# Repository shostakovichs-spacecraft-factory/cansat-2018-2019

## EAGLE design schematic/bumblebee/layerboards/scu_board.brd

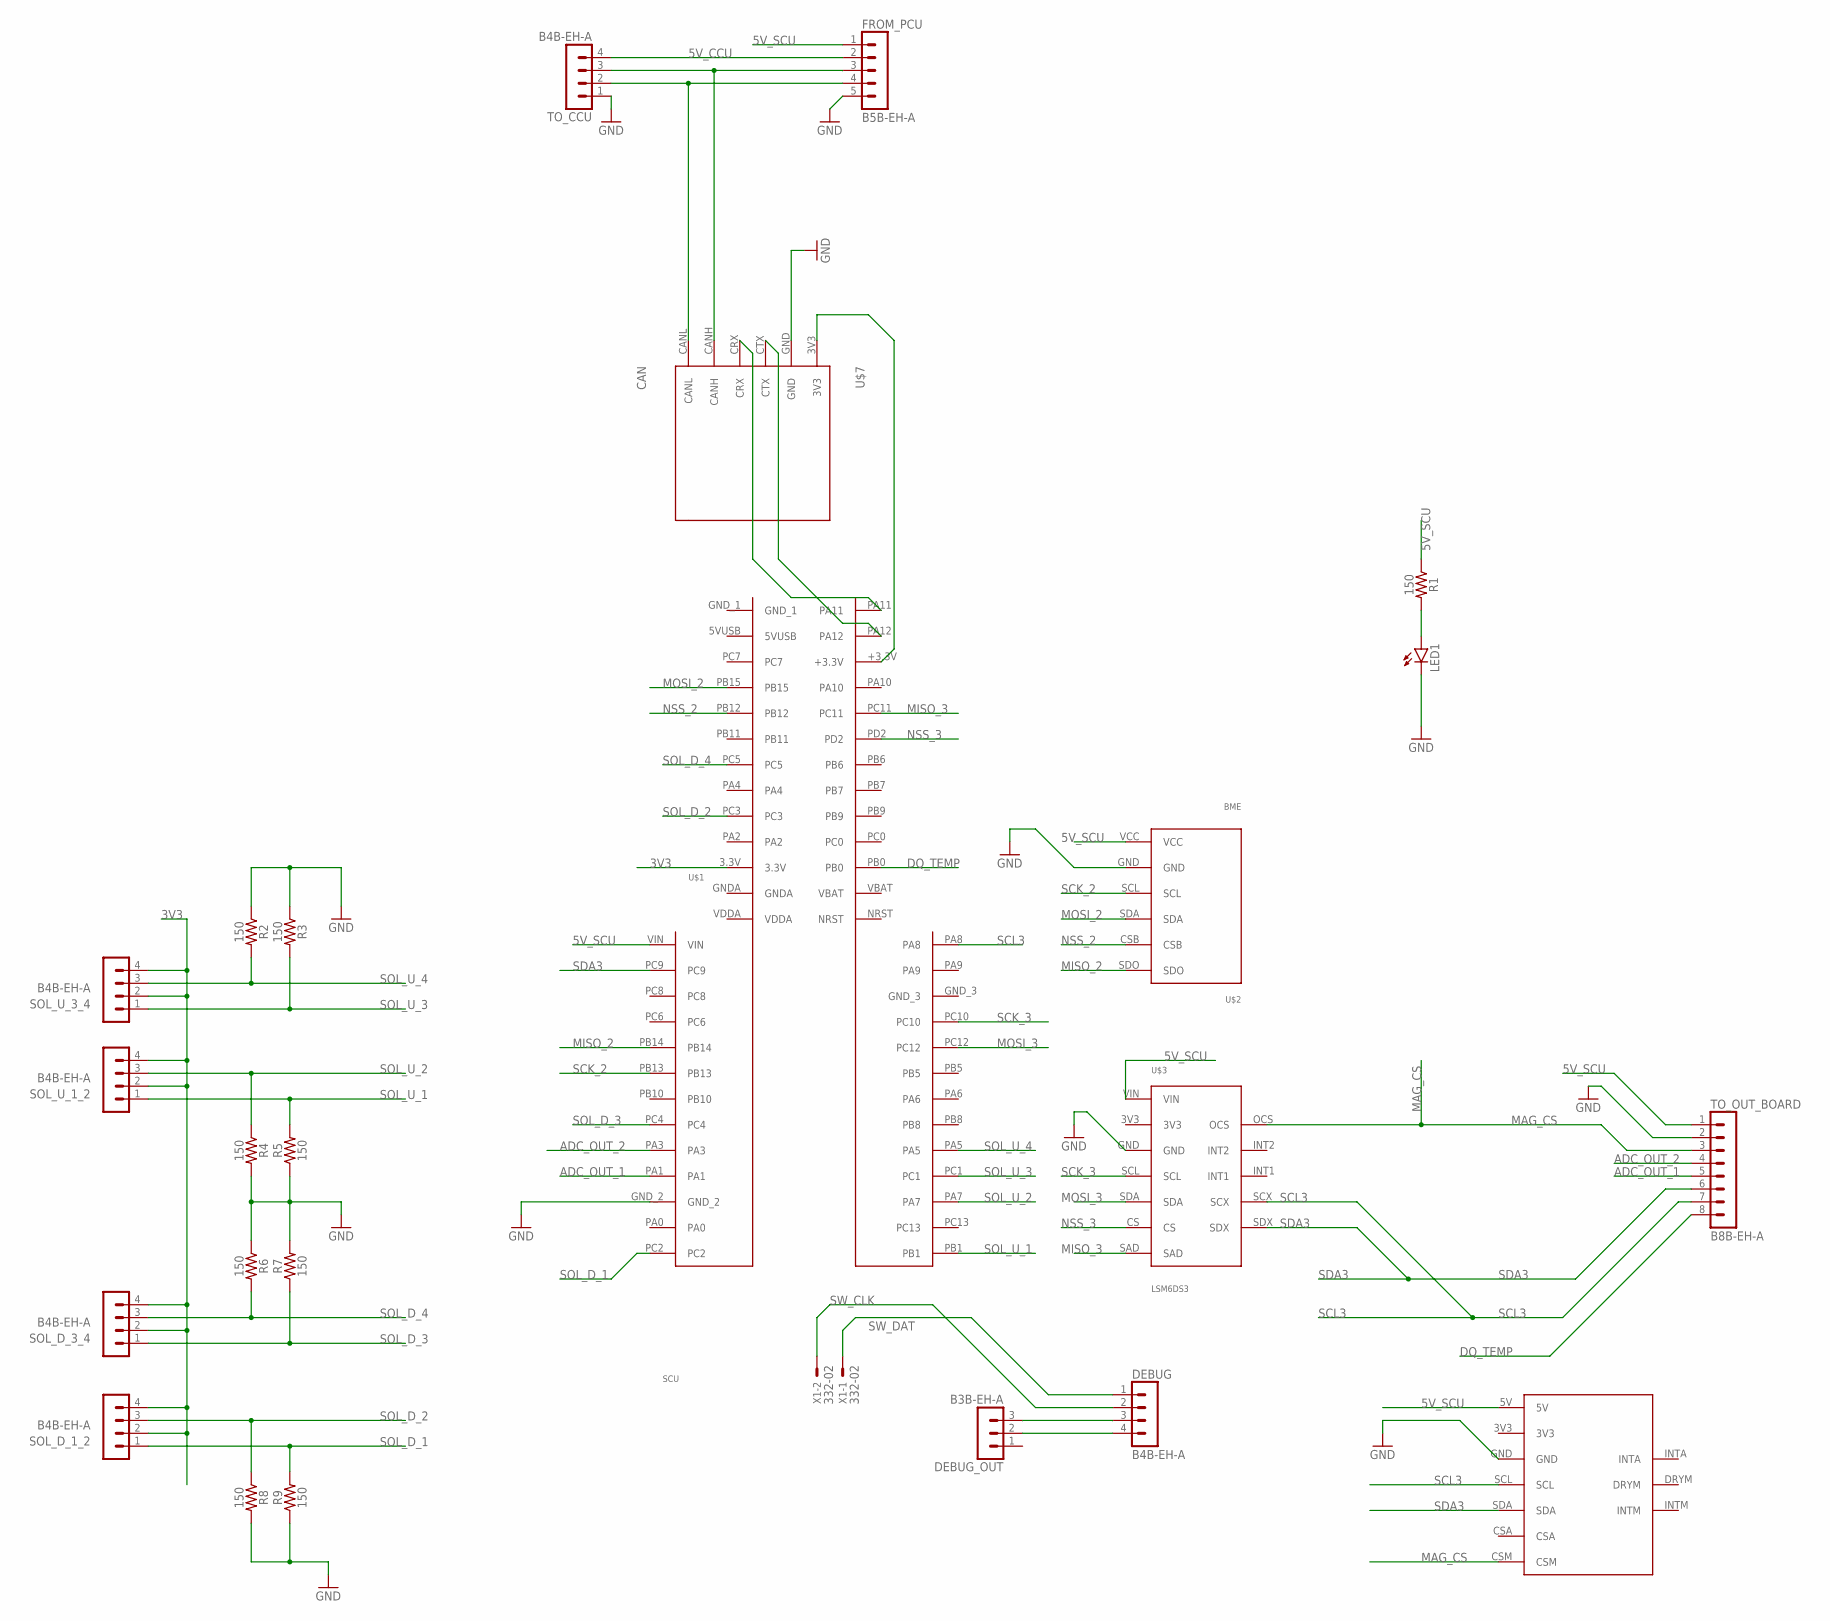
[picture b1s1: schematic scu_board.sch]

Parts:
DEBUG: B4B-EH-A
DEBUG_OUT: B3B-EH-A
FROM_PCU: B5B-EH-A
LED1: LED5MM
R1, R2, R3, R4, R5, R6, R7, R8, R9: 150; AXIAL-0.3
SOL_D_1_2, SOL_D_3_4: B4B-EH-A
SOL_U_1_2, SOL_U_3_4: B4B-EH-A
TO_CCU: B4B-EH-A
TO_OUT_BOARD: B8B-EH-A
U$1: SCU
U$2: BME
U$3: LSM6DS3
U$4: LSM303C
U$7: CAN
X1: 332-02

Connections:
3V3: SOL_D_1_2.2, SOL_D_1_2.4, SOL_D_3_4.2, SOL_D_3_4.4, SOL_U_1_2.2, SOL_U_1_2.4, SOL_U_3_4.2, SOL_U_3_4.4, U$1.3.3V
5V_CCU: FROM_PCU.2, TO_CCU.4
5V_SCU: FROM_PCU.1, R1.P$1 (1), TO_OUT_BOARD.1, U$1.VIN, U$2.VCC, U$3.VIN, U$4.5V
ADC_OUT_1: TO_OUT_BOARD.5, U$1.PA1
ADC_OUT_2: TO_OUT_BOARD.4, U$1.PA3
DQ_TEMP: TO_OUT_BOARD.8, U$1.PB0
GND: FROM_PCU.5, LED1.K (C), R2.P$1 (1), R3.P$1 (1), R4.P$2 (2), R5.P$1 (1), R6.P$1 (1), R7.P$2 (2), R8.P$2 (2), R9.P$1 (1), TO_CCU.1, TO_OUT_BOARD.2, U$1.GND_2, U$2.GND, U$3.GND, U$4.GND, U$7.GND
MAG_CS: TO_OUT_BOARD.3, U$3.OCS, U$4.CSM
MISO_2: U$1.PB14, U$2.SDO
MISO_3: U$1.PC11, U$3.SAD
MOSI_2: U$1.PB15, U$2.SDA
MOSI_3: U$1.PC12, U$3.SDA
unnamed: U$1.PA11, U$7.CRX
unnamed: U$1.PA12, U$7.CTX
unnamed: U$1.+3.3V, U$7.3V3
unnamed: LED1.A, R1.P$2 (2)
unnamed: FROM_PCU.3, TO_CCU.3, U$7.CANH
unnamed: FROM_PCU.4, TO_CCU.2, U$7.CANL
unnamed: DEBUG.3, DEBUG_OUT.3
unnamed: DEBUG.4, DEBUG_OUT.2
NSS_2: U$1.PB12, U$2.CSB
NSS_3: U$1.PD2, U$3.CS
SCK_2: U$1.PB13, U$2.SCL
SCK_3: U$1.PC10, U$3.SCL
SCL3: TO_OUT_BOARD.7, U$1.PA8, U$3.SCX, U$4.SCL
SDA3: TO_OUT_BOARD.6, U$1.PC9, U$3.SDX, U$4.SDA
SOL_D_1: R9.P$2 (2), SOL_D_1_2.1, U$1.PC2
SOL_D_2: R8.P$1 (1), SOL_D_1_2.3, U$1.PC3
SOL_D_3: R7.P$1 (1), SOL_D_3_4.1, U$1.PC4
SOL_D_4: R6.P$2 (2), SOL_D_3_4.3, U$1.PC5
SOL_U_1: R5.P$2 (2), SOL_U_1_2.1, U$1.PB1
SOL_U_2: R4.P$1 (1), SOL_U_1_2.3, U$1.PA7
SOL_U_3: R3.P$2 (2), SOL_U_3_4.1, U$1.PC1
SOL_U_4: R2.P$2 (2), SOL_U_3_4.3, U$1.PA5
SW_CLK: DEBUG.2, X1.2
SW_DAT: DEBUG.1, X1.1

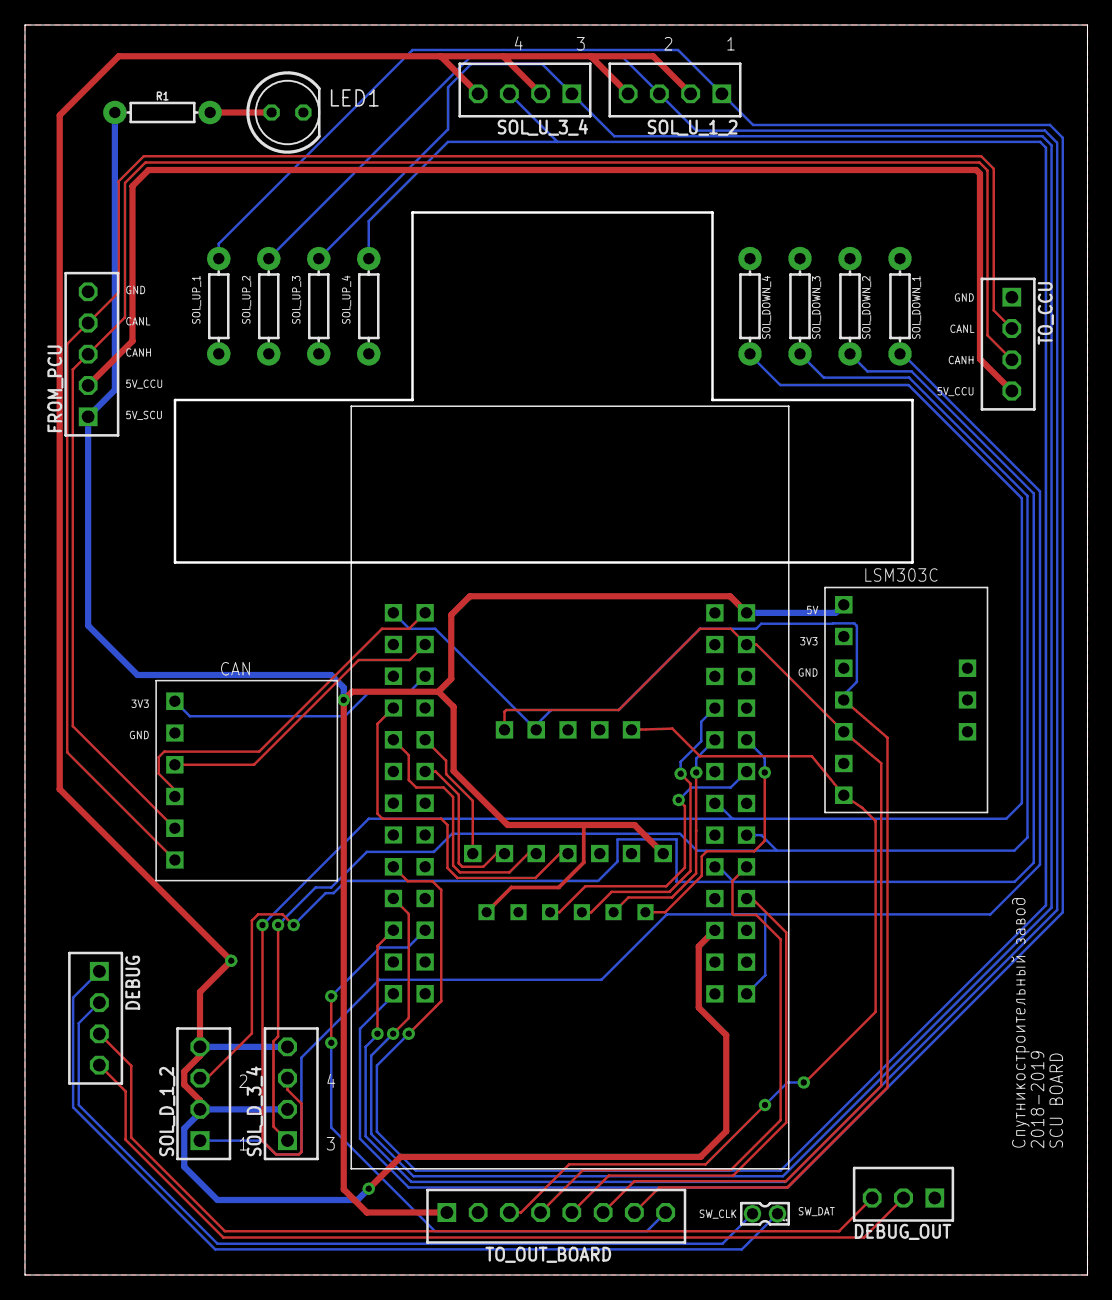
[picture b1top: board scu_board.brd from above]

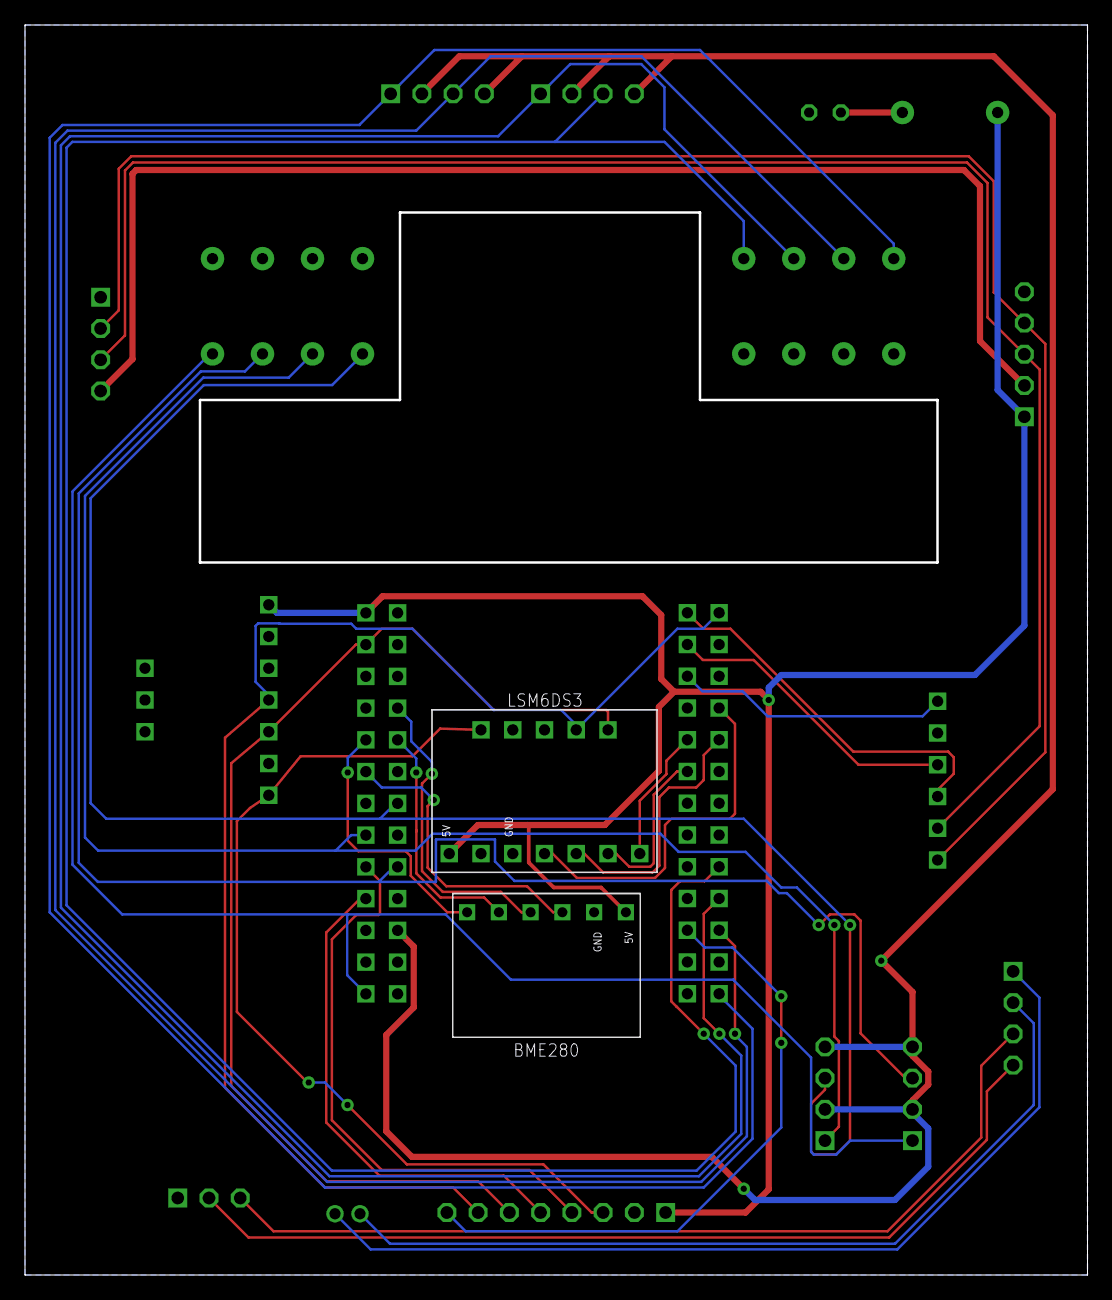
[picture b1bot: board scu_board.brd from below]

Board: 2 copper layers, 85.0 x 100.0 mm, 25 parts (2 on the bottom side), 36 nets.

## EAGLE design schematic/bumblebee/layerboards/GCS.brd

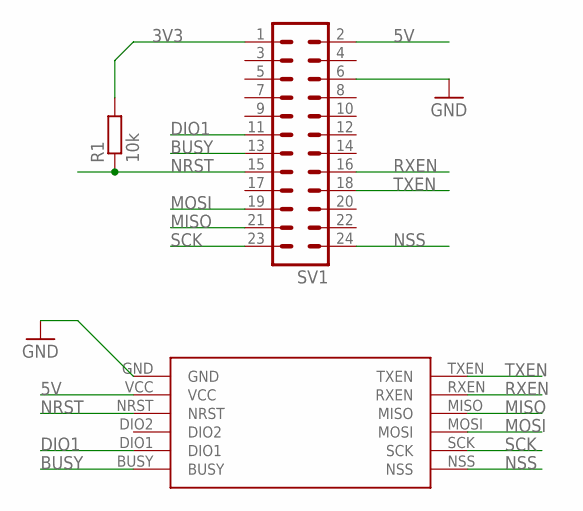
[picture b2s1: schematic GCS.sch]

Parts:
R1: 10k; 0207/10
SV1: MA12-2
U$1: E22_PLATE

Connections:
3V3: R1.2, SV1.1
5V: SV1.2, U$1.VCC
BUSY: SV1.13, U$1.BUSY
DIO1: SV1.11, U$1.DIO1
GND: SV1.6, U$1.GND
MISO: SV1.21, U$1.MISO
MOSI: SV1.19, U$1.MOSI
NRST: R1.1, SV1.15, U$1.NRST
NSS: SV1.24, U$1.NSS
RXEN: SV1.16, U$1.RXEN
SCK: SV1.23, U$1.SCK
TXEN: SV1.18, U$1.TXEN

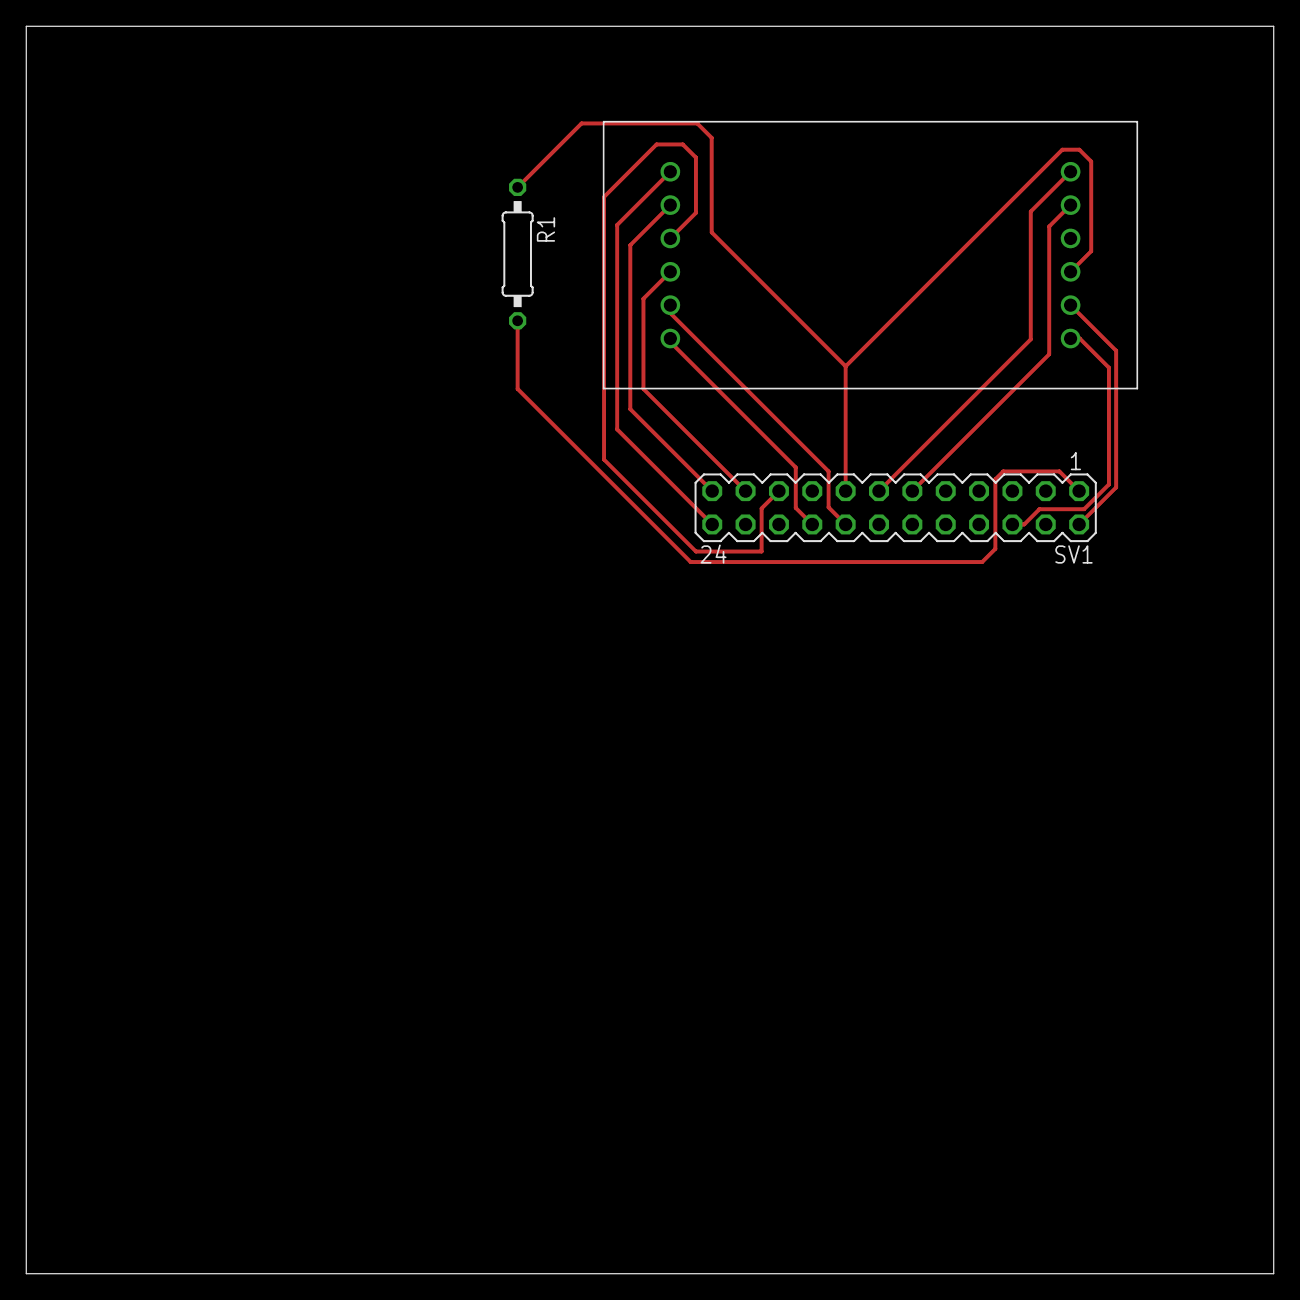
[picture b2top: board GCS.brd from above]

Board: 2 copper layers, 95.0 x 95.0 mm, 3 parts (0 on the bottom side), 12 nets.

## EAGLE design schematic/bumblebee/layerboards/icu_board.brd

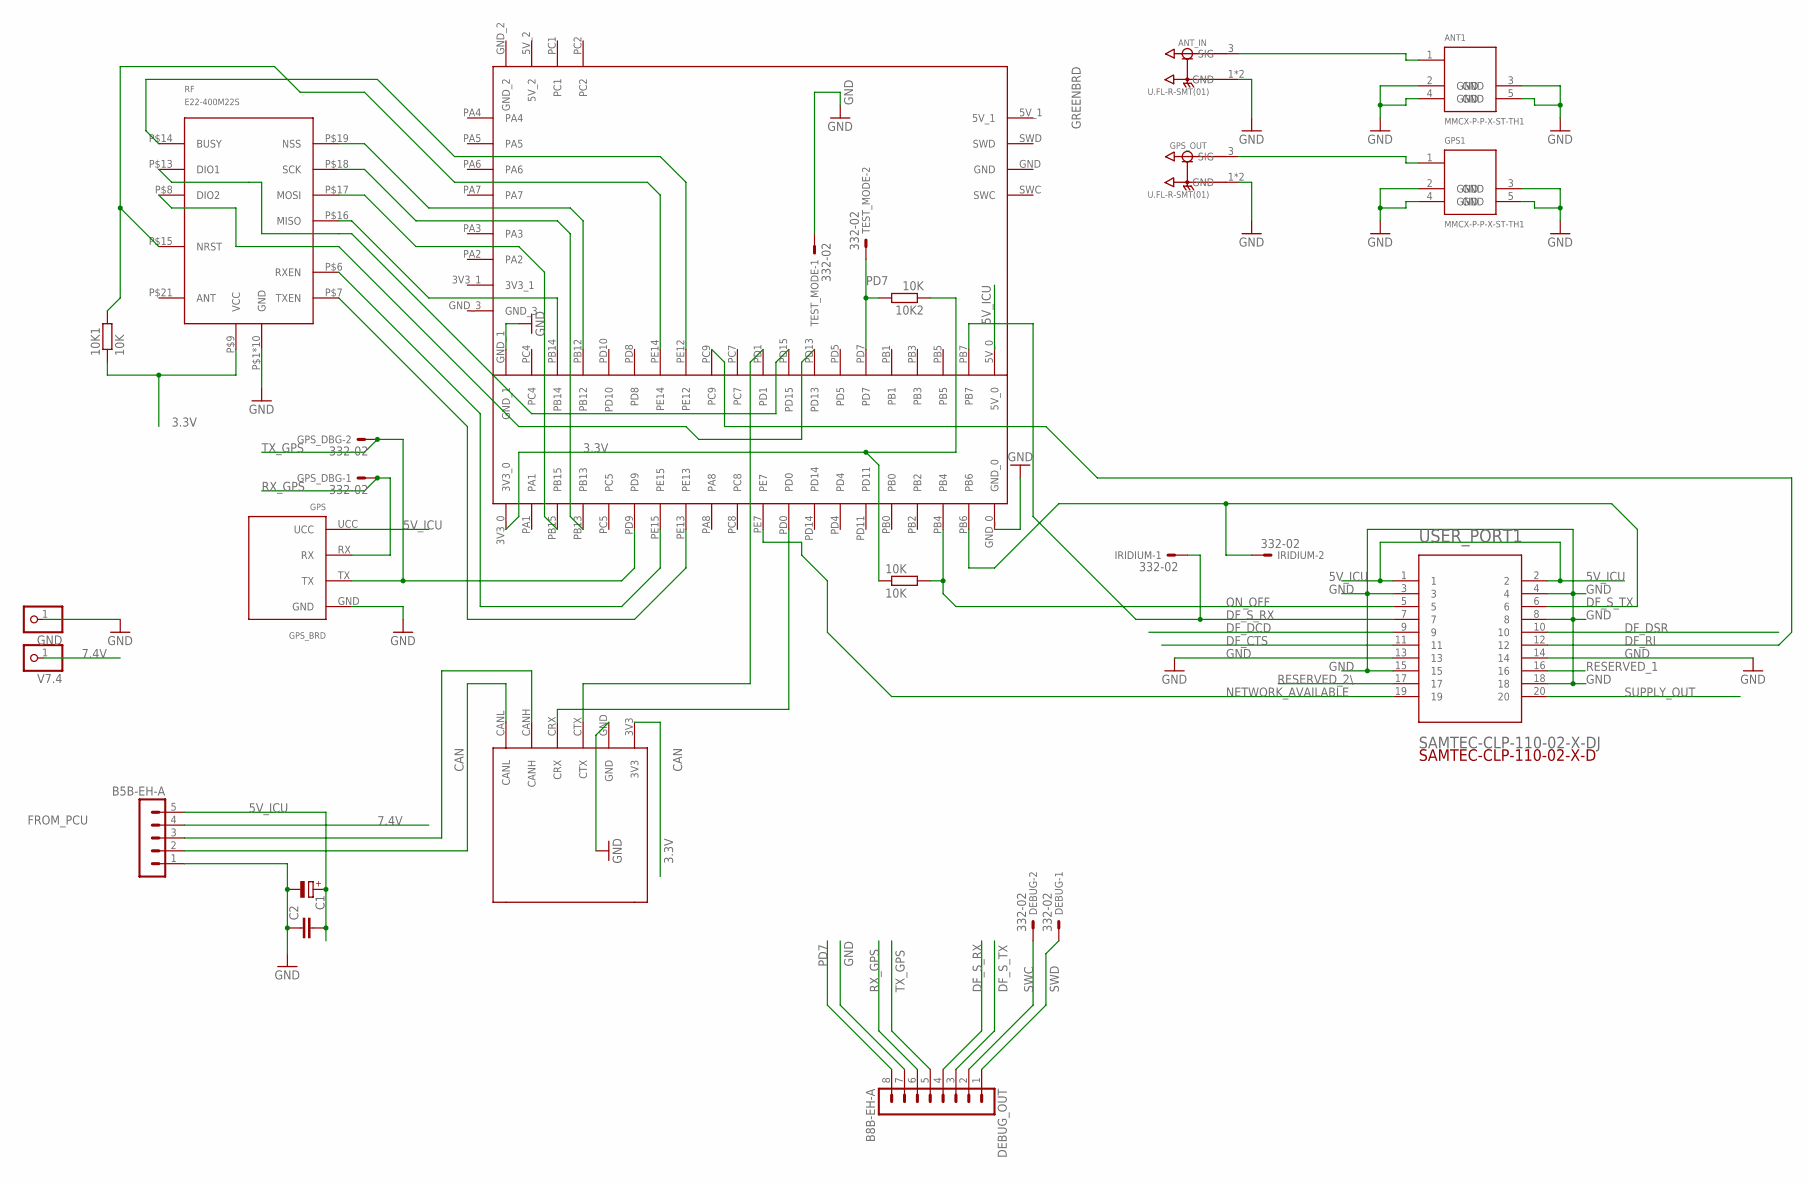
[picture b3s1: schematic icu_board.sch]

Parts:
10K, 10K1, 10K2: 10K; 0204/7
ANT1: MMCX-P-P-X-ST-TH1
ANT_IN: U.FL-R-SMT(01); HRS_U.FL-R-SMT(01)
C1: CPOL-EUE3.5-8; E3,5-8
C2: C2.5/2; C2.5-2
CAN: CAN
DEBUG: 332-02
DEBUG_OUT: B8B-EH-A
FROM_PCU: B5B-EH-A
GND: PINHD-1X1; 1X01
GPS1: MMCX-P-P-X-ST-TH1
GPS_BRD: GPS
GPS_DBG: 332-02
GPS_OUT: U.FL-R-SMT(01); HRS_U.FL-R-SMT(01)
GREENBRD: ICU
IRIDIUM: 332-02
RF: E22-400M22S
TEST_MODE: 332-02
USER_PORT1: SAMTEC-CLP-110-02-X-DJ; SAMTEC-CLP-110-02-X-D
V7.4: PINHD-1X1; 1X01

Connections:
3.3V: 10K.1, 10K1.1, 10K2.1, CAN.3V3, GREENBRD.3V3_0, RF.P$9 (VCC)
5V_ICU: C1.+, C2.2, FROM_PCU.5, GPS_BRD.UCC, GREENBRD.5V_0, USER_PORT1.1, USER_PORT1.2
7.4V: FROM_PCU.4, V7.4.1
DF_CTS: USER_PORT1.11
DF_DCD: USER_PORT1.9
DF_DSR: USER_PORT1.10
DF_RI: GREENBRD.PC9, USER_PORT1.12
DF_S_RX: DEBUG_OUT.4, GREENBRD.PB7, IRIDIUM.1, USER_PORT1.7
DF_S_TX: DEBUG_OUT.3, GREENBRD.PB6, IRIDIUM.2, USER_PORT1.6
GND: ANT1.2 (GND), ANT1.3 (GND), ANT1.4 (GND), ANT1.5 (GND), ANT_IN.1 (GND), ANT_IN.2 (GND), C1.-, C2.1, CAN.GND, DEBUG_OUT.7, FROM_PCU.1, GND.1, GPS1.2 (GND), GPS1.3 (GND), GPS1.4 (GND), GPS1.5 (GND), GPS_BRD.GND, GPS_OUT.1 (GND), GPS_OUT.2 (GND), GREENBRD.GND_0, GREENBRD.GND_1, RF.P$1 (GND), RF.P$2 (GND), RF.P$3 (GND), RF.P$4 (GND), RF.P$5 (GND), RF.P$10 (GND), RF.P$11 (GND), RF.P$12 (GND), RF.P$20 (GND), RF.P$22 (GND), TEST_MODE.1, USER_PORT1.3, USER_PORT1.4, USER_PORT1.8, USER_PORT1.13, USER_PORT1.14, USER_PORT1.15, USER_PORT1.18
unnamed: CAN.CANH, FROM_PCU.3
unnamed: GREENBRD.PB12, RF.P$19 (NSS)
unnamed: CAN.CANL, FROM_PCU.2
unnamed: ANT1.1, ANT_IN.3 (SIG)
unnamed: GPS1.1, GPS_OUT.3 (SIG)
unnamed: GREENBRD.PE15, RF.P$6 (RXEN)
unnamed: GREENBRD.PB13, RF.P$18 (SCK)
unnamed: CAN.CRX, GREENBRD.PD0
unnamed: CAN.CTX, GREENBRD.PD1
unnamed: GREENBRD.PD15, RF.P$13 (DIO1)
unnamed: GREENBRD.PD13, RF.P$8 (DIO2)
unnamed: GREENBRD.PB15, RF.P$17 (MOSI)
unnamed: GREENBRD.PB14, RF.P$16 (MISO)
unnamed: GREENBRD.PE12, RF.P$14 (BUSY)
unnamed: 10K1.2, GREENBRD.PE14, RF.P$15 (NRST)
unnamed: GREENBRD.PE13, RF.P$7 (TXEN)
NETWORK_AVAILABLE: GREENBRD.PE7, USER_PORT1.19
ON_OFF: 10K.2, GREENBRD.PB4, USER_PORT1.5
PD7: 10K2.2, DEBUG_OUT.8, GREENBRD.PD7, TEST_MODE.2
RESERVED_1: USER_PORT1.16
RESERVED_2\: USER_PORT1.17
RX_GPS: DEBUG_OUT.6, GPS_BRD.RX, GPS_DBG.1
SUPPLY_OUT: USER_PORT1.20
SWC: DEBUG.2, DEBUG_OUT.2
SWD: DEBUG.1, DEBUG_OUT.1
TX_GPS: DEBUG_OUT.5, GPS_BRD.TX, GPS_DBG.2, GREENBRD.PD9

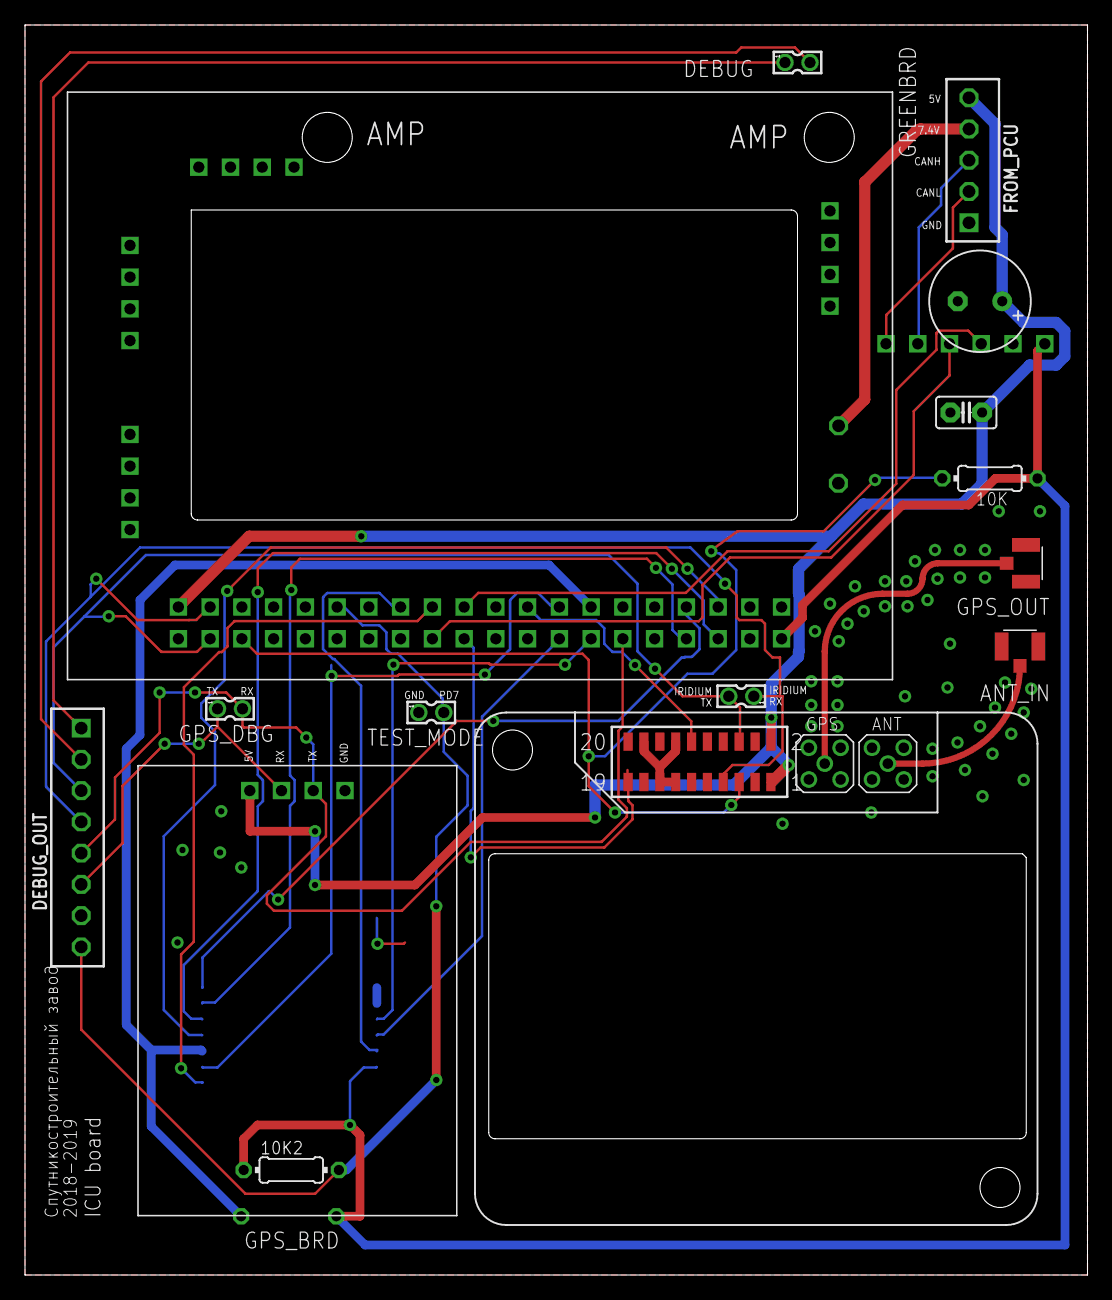
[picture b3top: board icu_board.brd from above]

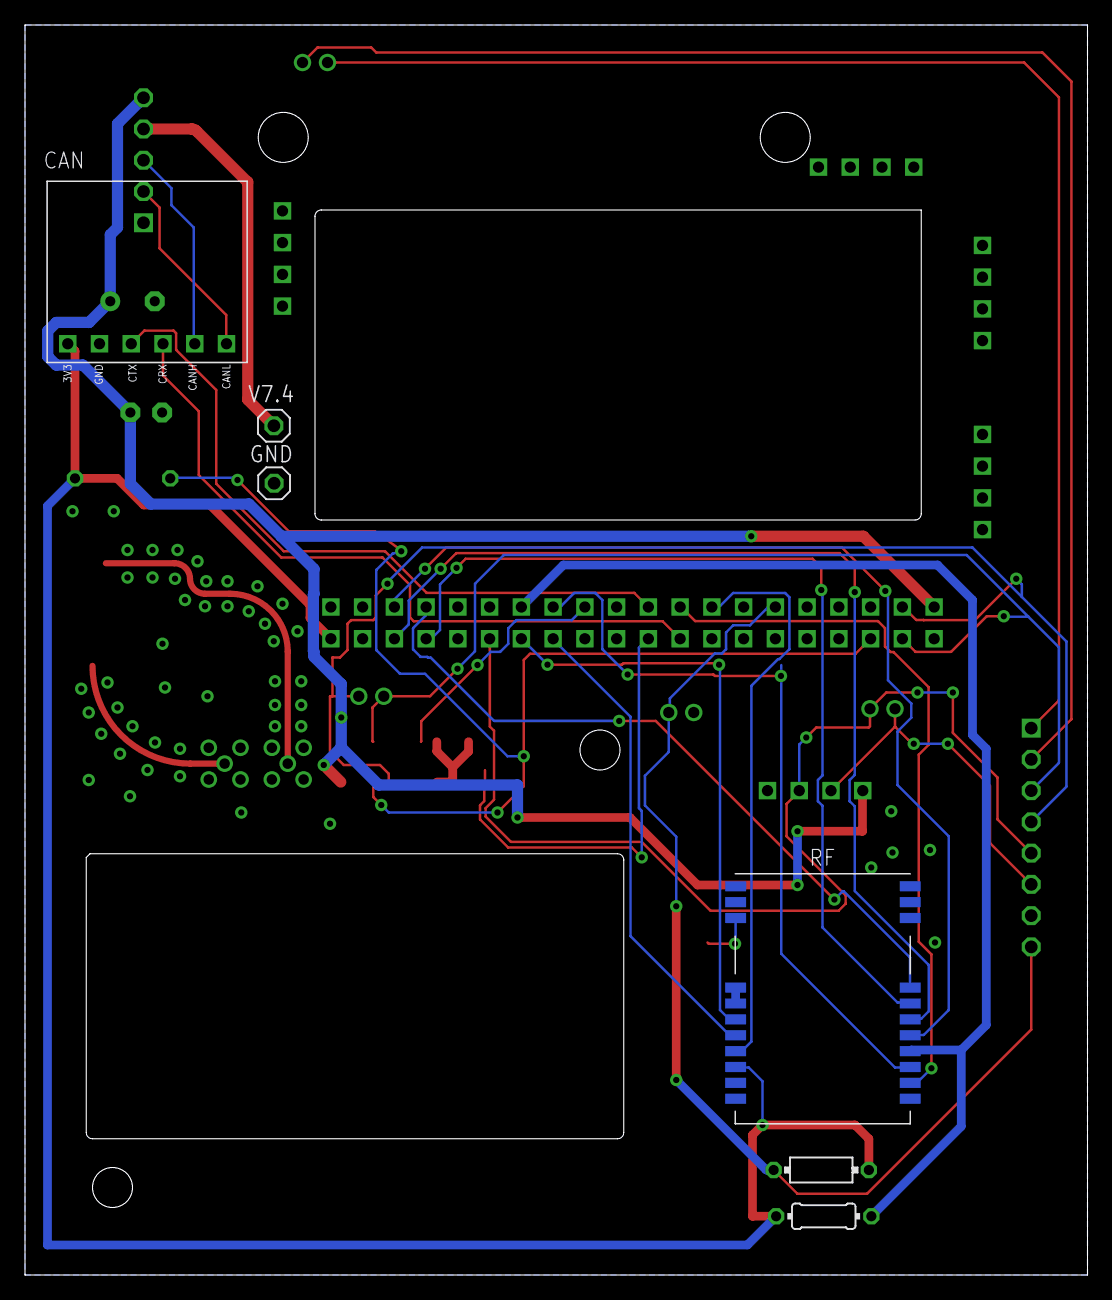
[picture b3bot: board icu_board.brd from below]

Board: 2 copper layers, 85.0 x 100.0 mm, 22 parts (5 on the bottom side), 30 nets.

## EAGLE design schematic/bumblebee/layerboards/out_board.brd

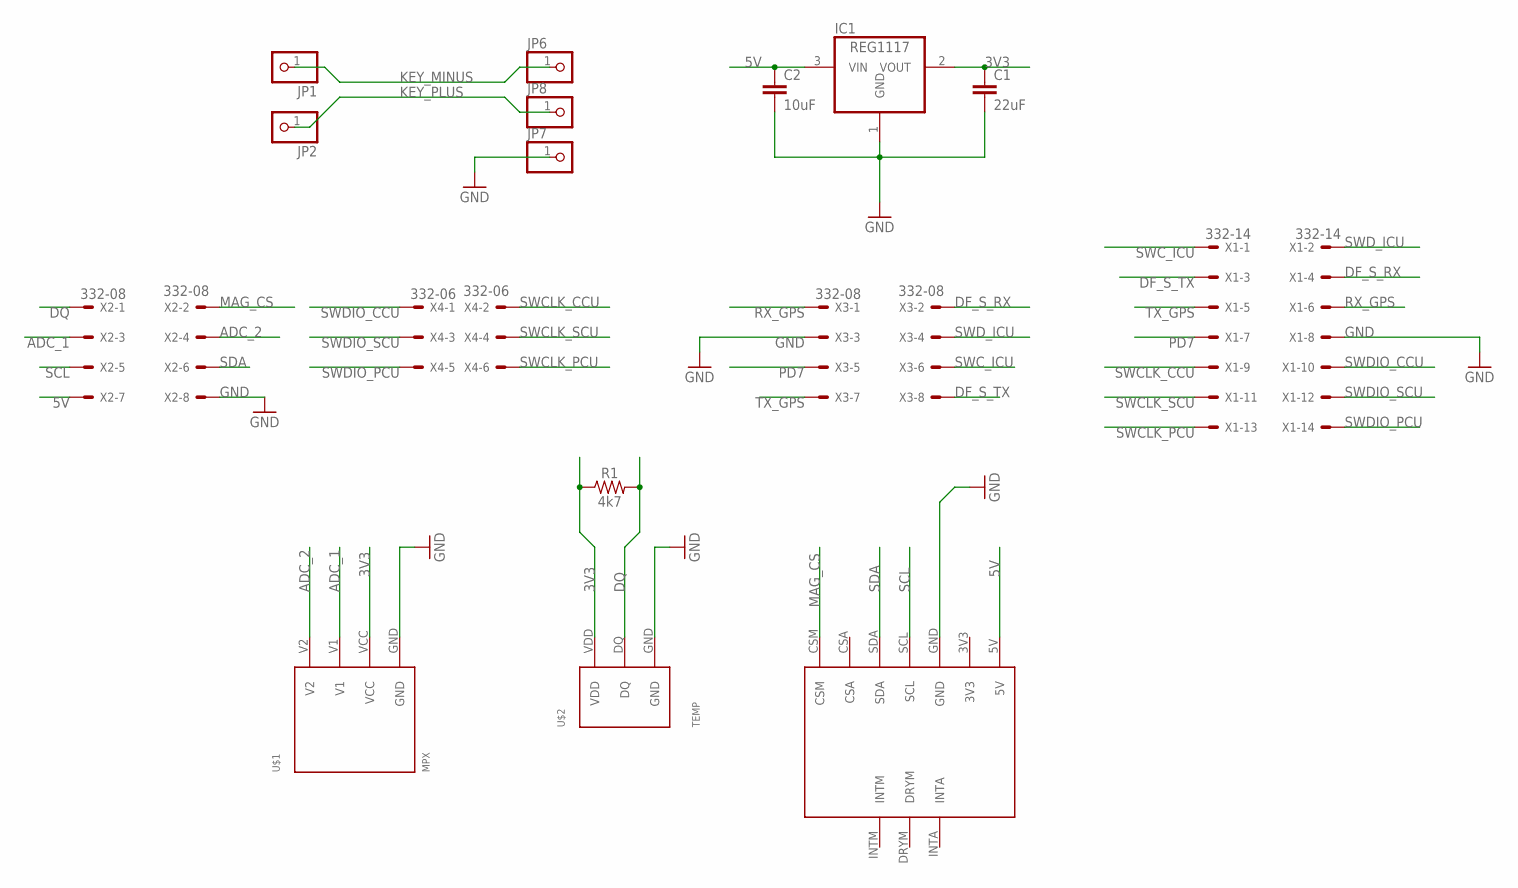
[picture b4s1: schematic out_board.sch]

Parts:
C1: 22uF; 0805
C2: 10uF; 0805
IC1: REG1117; SOT223
JP1, JP2, JP6, JP7, JP8: PINHD-1X1; 1X01
R1: 4k7; AXIAL-0.3
U$1: MPX
U$2: TEMP
U$3: LSM303C
X1: 332-14
X2, X3: 332-08
X4: 332-06

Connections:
3V3: C1.1, IC1.2 (VOUT), R1.P$1 (1), U$1.VCC, U$2.VDD
5V: C2.1, IC1.3 (VIN), U$3.5V, X2.7
ADC_1: U$1.V1, X2.3
ADC_2: U$1.V2, X2.4
DF_S_RX: X1.4, X3.2
DF_S_TX: X1.3, X3.8
DQ: R1.P$2 (2), U$2.DQ, X2.1
GND: C1.2, C2.2, IC1.1 (GND), JP7.1, U$1.GND, U$2.GND, U$3.GND, X1.8, X2.8, X3.3
KEY_MINUS: JP1.1, JP6.1
KEY_PLUS: JP2.1, JP8.1
MAG_CS: U$3.CSM, X2.2
PD7: X1.7, X3.5
RX_GPS: X1.6, X3.1
SCL: U$3.SCL, X2.5
SDA: U$3.SDA, X2.6
SWCLK_CCU: X1.9, X4.2
SWCLK_PCU: X1.13, X4.6
SWCLK_SCU: X1.11, X4.4
SWC_ICU: X1.1, X3.6
SWDIO_CCU: X1.10, X4.1
SWDIO_PCU: X1.14, X4.5
SWDIO_SCU: X1.12, X4.3
SWD_ICU: X1.2, X3.4
TX_GPS: X1.5, X3.7

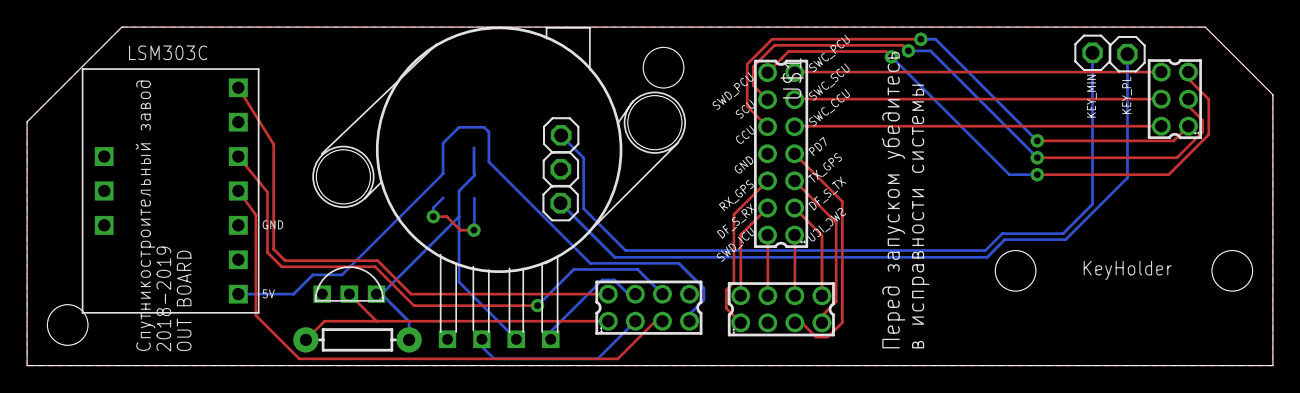
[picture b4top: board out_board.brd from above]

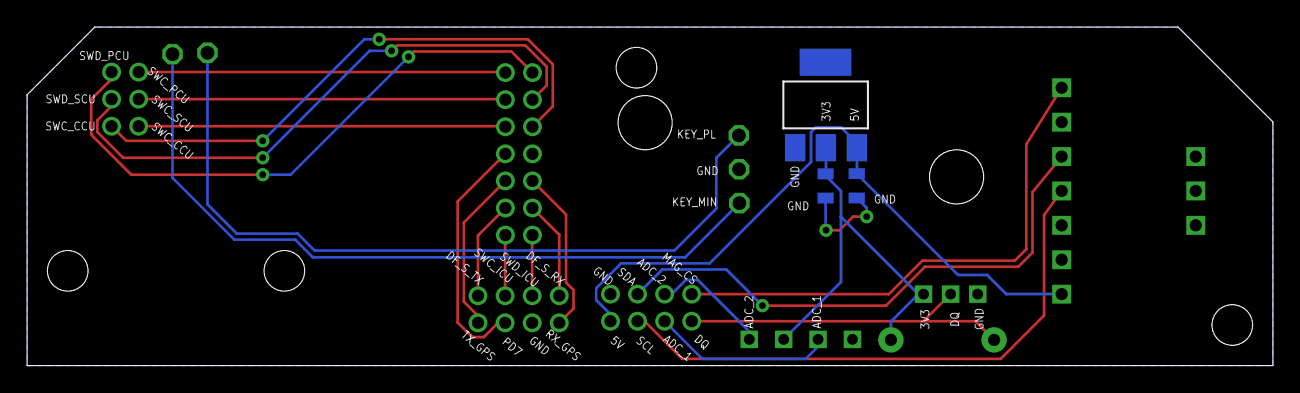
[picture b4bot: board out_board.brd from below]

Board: 2 copper layers, 92.0 x 25.0 mm, 16 parts (3 on the bottom side), 24 nets.

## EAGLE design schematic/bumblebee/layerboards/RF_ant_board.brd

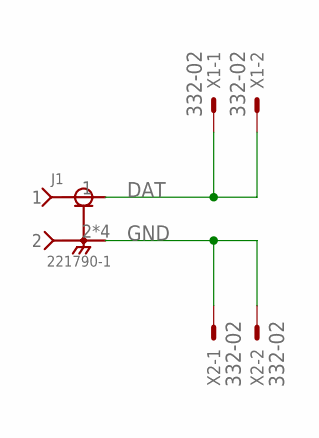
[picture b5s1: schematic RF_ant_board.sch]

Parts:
J1: 221790-1; TE_221790-1
X1, X2: 332-02

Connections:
DAT: J1.1, X1.1, X1.2
GND: J1.2, J1.3 (2), J1.4 (2), J1.5 (2), X2.1, X2.2

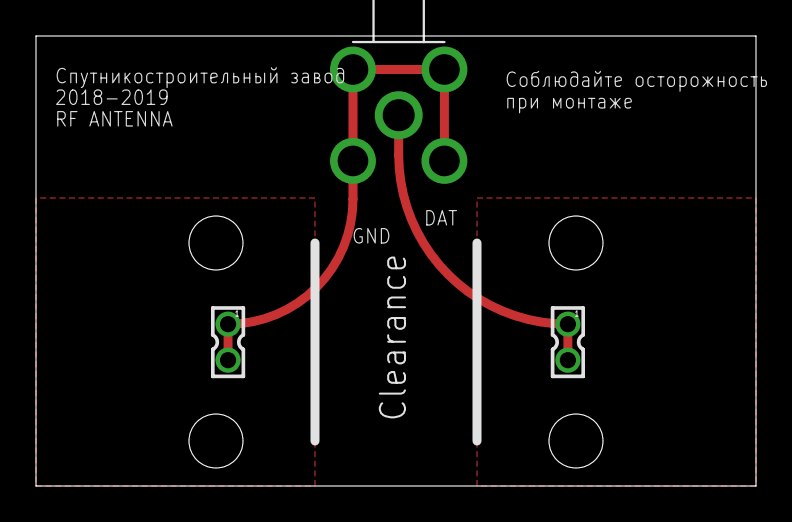
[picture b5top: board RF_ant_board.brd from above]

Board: 2 copper layers, 40.0 x 25.0 mm, 3 parts (0 on the bottom side), 2 nets.

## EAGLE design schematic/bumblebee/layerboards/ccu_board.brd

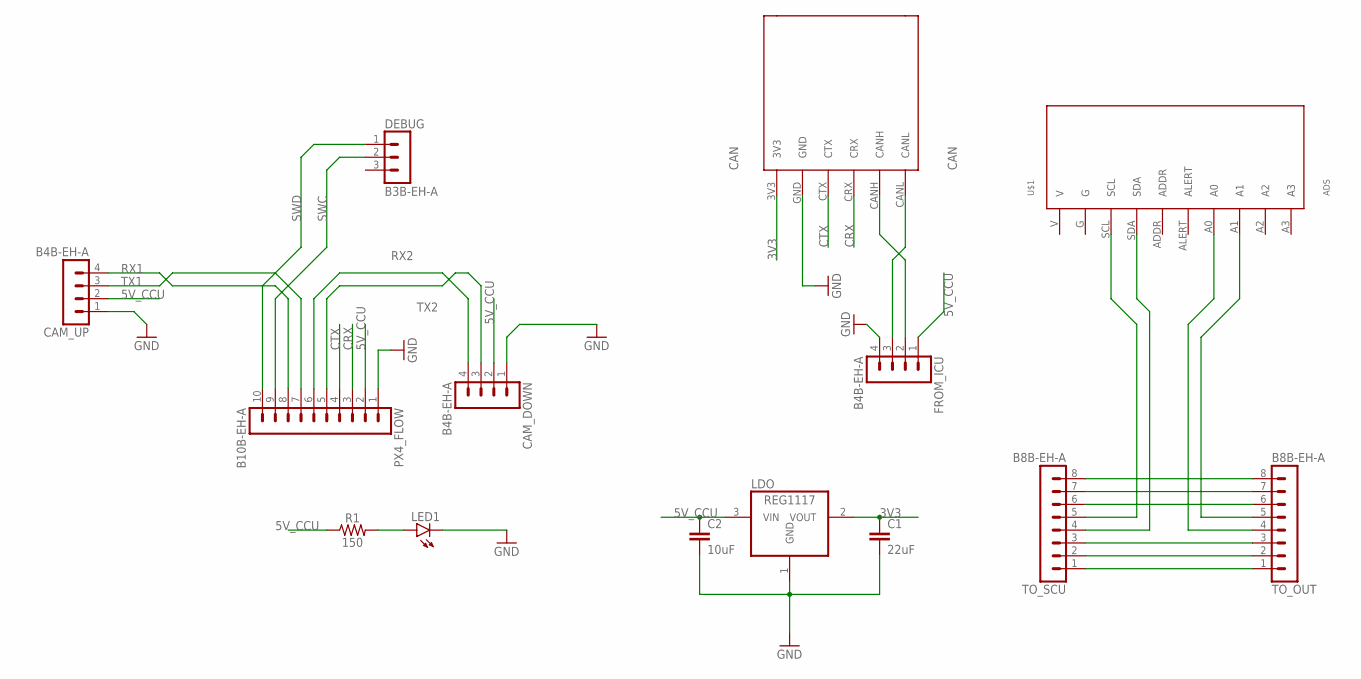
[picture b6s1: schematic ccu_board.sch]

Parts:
C1: 22uF; 0805
C2: 10uF; 0805
CAM_DOWN: B4B-EH-A
CAM_UP: B4B-EH-A
CAN: CAN
DEBUG: B3B-EH-A
FROM_ICU: B4B-EH-A
LDO: REG1117; SOT223
LED1: LED5MM
PX4_FLOW: B10B-EH-A
R1: 150; AXIAL-0.3
TO_OUT: B8B-EH-A
TO_SCU: B8B-EH-A
U$1: ADS

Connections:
3V3: C1.1, CAN.3V3, LDO.2 (VOUT)
5V_CCU: C2.1, CAM_DOWN.2, CAM_UP.2, FROM_ICU.1, LDO.3 (VIN), PX4_FLOW.2, R1.P$1 (1)
CRX: CAN.CRX, PX4_FLOW.3
CTX: CAN.CTX, PX4_FLOW.4
GND: C1.2, C2.2, CAM_DOWN.1, CAM_UP.1, CAN.GND, FROM_ICU.4, LDO.1 (GND), LED1.K (C), PX4_FLOW.1
unnamed: TO_OUT.8, TO_SCU.8
unnamed: TO_OUT.7, TO_SCU.7
unnamed: TO_OUT.6, TO_SCU.6
unnamed: TO_OUT.3, TO_SCU.3
unnamed: TO_OUT.2, TO_SCU.2
unnamed: CAN.CANL, FROM_ICU.3
unnamed: TO_OUT.1, TO_SCU.1
unnamed: CAN.CANH, FROM_ICU.2
unnamed: TO_SCU.5, U$1.SCL
unnamed: TO_SCU.4, U$1.SDA
unnamed: LED1.A, R1.P$2 (2)
unnamed: TO_OUT.5, U$1.A1
unnamed: TO_OUT.4, U$1.A0
RX1: CAM_UP.4, PX4_FLOW.8
RX2: CAM_DOWN.4, PX4_FLOW.6
SWC: DEBUG.2, PX4_FLOW.9
SWD: DEBUG.1, PX4_FLOW.10
TX1: CAM_UP.3, PX4_FLOW.7
TX2: CAM_DOWN.3, PX4_FLOW.5

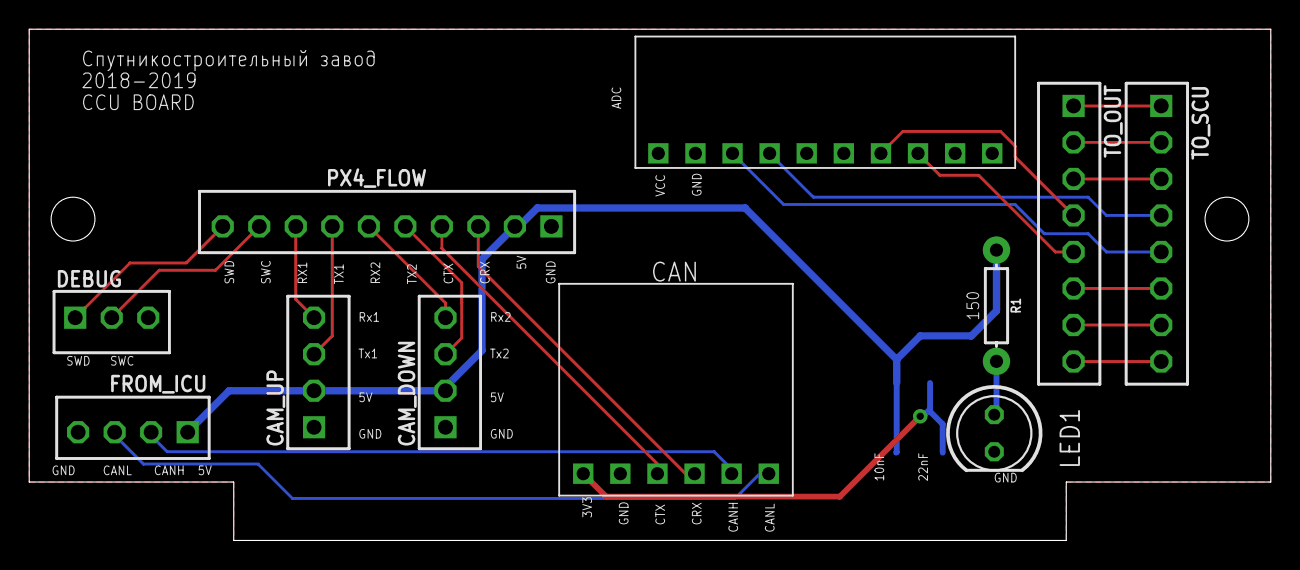
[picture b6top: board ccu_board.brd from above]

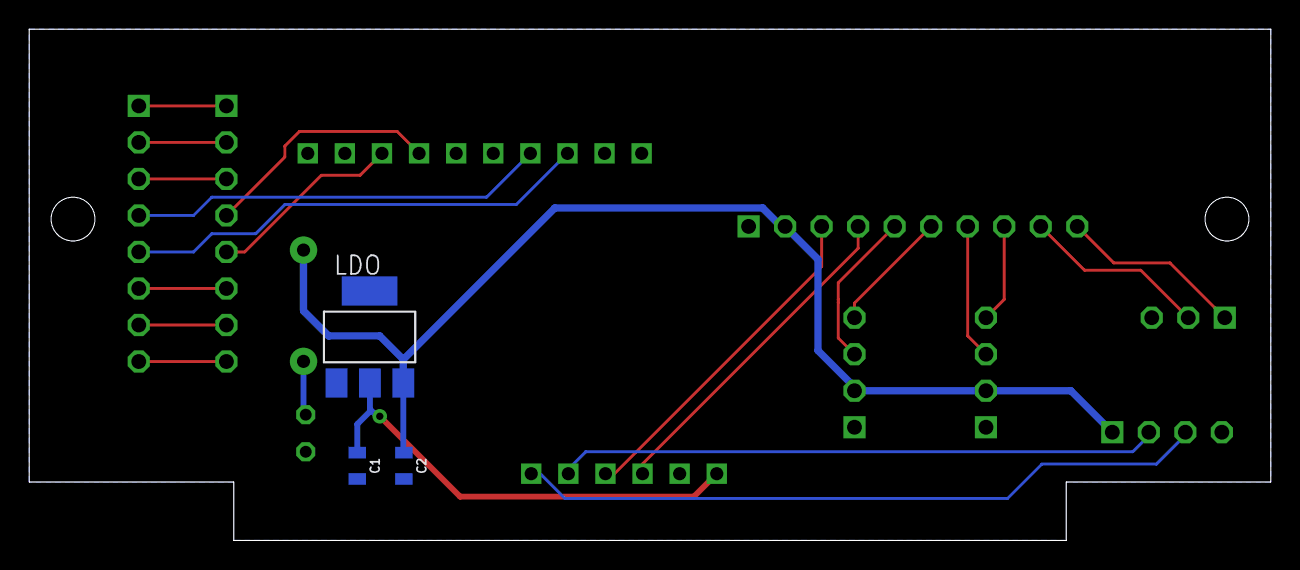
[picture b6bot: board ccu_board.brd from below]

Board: 2 copper layers, 85.0 x 35.0 mm, 14 parts (3 on the bottom side), 24 nets.

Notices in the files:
parts and their libraries:
con-jst-eh: Copyright (C) 2016, Bob Starr
SparkFun-Capacitors: Licensing: Creative Commons ShareAlike 4.0 International - https://creativecommons.org/licenses/by-sa/4.0
